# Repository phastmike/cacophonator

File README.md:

# Cacophonator

This repository contains the [KiCad](https://www.kicad.org/) project of a try at recreating an instance of
**[the cacophonator](https://www.theremin.us/Circuit_Library/cacophonator.html)**
by Arthur Harrison. 

### Build iteration

#### V1 THT

- Using THT (Through-hole) components
- Designed for [JSL 166x116x70mm Box](https://www.leroymerlin.pt/produtos/caixa-estanque-10-boquilhas-153x102x67mm-ip66-cinzento-jsl-15918315.html)

## Modifications to the original
 
- Added a potentiometer to control the output amplitude (volume)
   - Should be a **logaritmic (log) potentiometer**
- Added DC Input jack with diodes for multiple, concurrent, power sources
   - Battery (9V)
   - DC IN (9 or 12V))

## Notes

Designed with KiCad 9.0 

Top cover layout tryout

Box (166x116x70mm)

### BOM - Bill of Materials

[BOM](icad/outputs/v1/cacophonator-bom.ods)

### Links

- https://www.theremin.us/Circuit_Library/cacophonator.html
- https://syntherjack.net/catophonator/
- https://vitrolxul.mitiendanube.com/productos/cacophonator/
- http://analogmodularsystem.blogspot.com/2014/01/cacophonator-i.html
- https://milwaukeemakerspace.org/2011/09/cacophonator/
- https://beavisaudio.com/projects/cmossynthesizers/
- https://blacblob.qsdf.org/2018/10/03/cacophonator/
- https://static.flickr.com/100/312128991_4e7175fa40.jpg?v=0
- https://www.ti.com/lit/an/slyt336/slyt336.pdf?ts=1739280684395
- https://www.flickr.com/photos/53178019@N00/page2
- https://electro-music.com/forum/post-328159.html
- https://dimsos.dk/cacophonator/cacophonator-take-2-v8/
- https://www.matrixsynth.com/search/label/Cacophonator
- http://www.subtlenoisemaker.com/cacophonator_noir.html

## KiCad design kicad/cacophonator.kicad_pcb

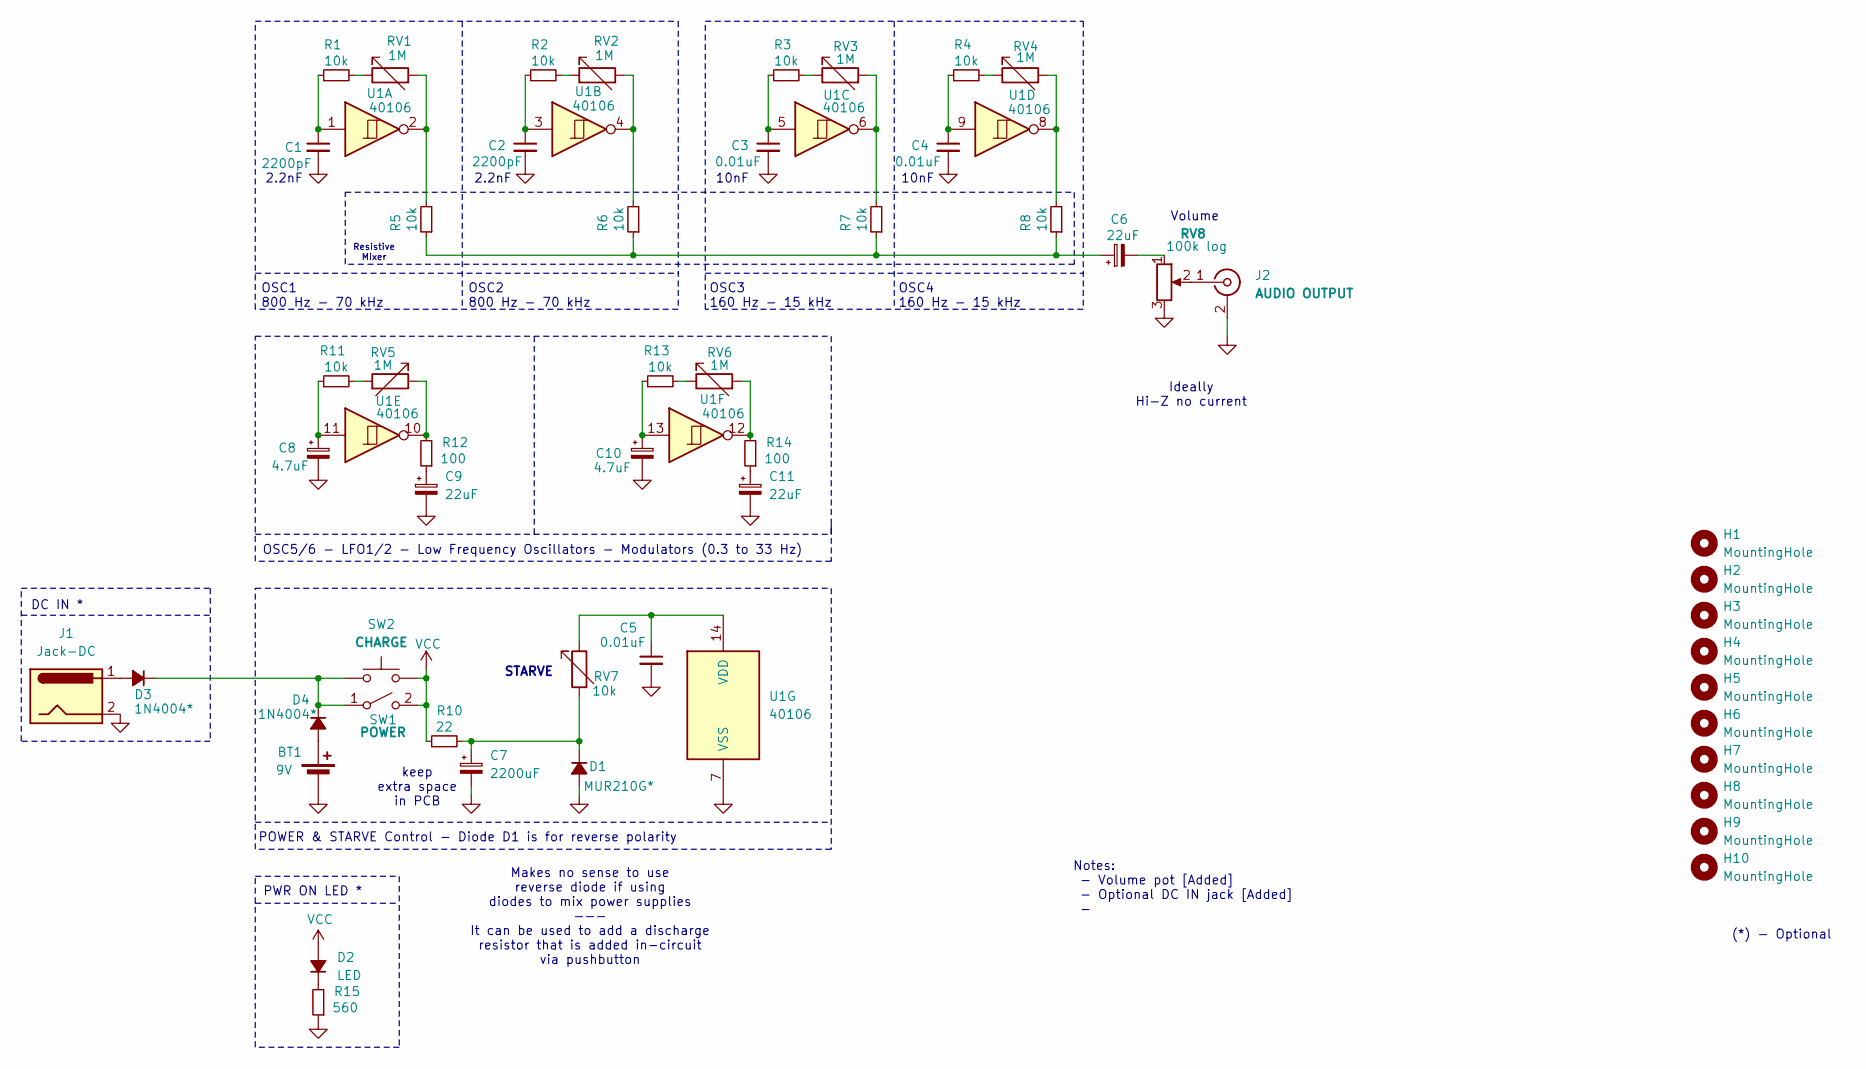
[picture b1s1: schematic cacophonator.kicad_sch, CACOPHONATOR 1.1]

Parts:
BT1: 9V; JST_PH_B2B-PH-K_1x02_P2.00mm_Vertical
C1, C2: 2200pF; C_Disc_D7.0mm_W2.5mm_P5.00mm
C3, C4, C5: 0.01uF; C_Disc_D7.0mm_W2.5mm_P5.00mm
C6: 22uF; CP_Radial_D4.0mm_P2.00mm
C7: 2200uF; CP_Radial_D10.0mm_P5.00mm
C8, C10: 4.7uF; CP_Radial_D4.0mm_P2.00mm
C9, C11: 22uF; CP_Radial_D7.5mm_P2.50mm
D1: MUR210G*; D_DO-35_SOD27_P7.62mm_Horizontal
D2: LED; JST_PH_B2B-PH-K_1x02_P2.00mm_Vertical
D3, D4: 1N4004*; D_DO-35_SOD27_P7.62mm_Horizontal
H1, H2, H3, H4, H5, H6, H7, H8, H9, H10: MountingHole; MountingHole_3.2mm_M3_ISO7380_Pad
J1: Jack-DC; JST_PH_B2B-PH-K_1x02_P2.00mm_Vertical
J2: AUDIO OUTPUT; JST_PH_B2B-PH-K_1x02_P2.00mm_Vertical
R1, R2, R3, R4, R5, R6, R7, R8, R11, R13: 10k; R_Axial_DIN0204_L3.6mm_D1.6mm_P5.08mm_Horizontal
R10: 22; R_Axial_DIN0204_L3.6mm_D1.6mm_P5.08mm_Horizontal
R12, R14: 100; R_Axial_DIN0204_L3.6mm_D1.6mm_P5.08mm_Horizontal
R15: 560; R_Axial_DIN0204_L3.6mm_D1.6mm_P5.08mm_Horizontal
RV1, RV2, RV3, RV4, RV5, RV6: 1M; JST_PH_B2B-PH-K_1x02_P2.00mm_Vertical
RV7: 10k; JST_PH_B2B-PH-K_1x02_P2.00mm_Vertical
RV8: 100k log; JST_PH_B3B-PH-K_1x03_P2.00mm_Vertical
SW1: POWER; JST_PH_B2B-PH-K_1x02_P2.00mm_Vertical
SW2: CHARGE; JST_PH_B2B-PH-K_1x02_P2.00mm_Vertical
U1: 40106; DIP-14_W7.62mm

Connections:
GND: BT1.2 (-), C1.2, C2.2, C3.2, C4.2, C5.2, C7.2, C8.2, C9.2, C10.2, C11.2, D1.2 (A), J1.2, J2.2 (Ext), R15.1, RV8.3, U1.7 (VSS)
unnamed: BT1.1 (+), D4.2 (A)
unnamed: C1.1, R1.1, U1.1
unnamed: C2.1, R2.1, U1.3
unnamed: C3.1, R3.1, U1.5
unnamed: C4.1, R4.1, U1.9
unnamed: C6.1, R5.1, R6.1, R7.1, R8.1
unnamed: C6.2, RV8.1
unnamed: C8.1, R11.1, U1.11
unnamed: C9.1, R12.1
unnamed: C10.1, R13.1, U1.13
unnamed: C11.1, R14.1
unnamed: C7.1, D1.1 (K), R10.2, RV7.2
unnamed: D2.1 (K), R15.2
unnamed: D3.2 (A), J1.1
unnamed: D3.1 (K), D4.1 (K), SW1.1 (A), SW2.1
unnamed: J2.1 (In), RV8.2
unnamed: R1.2, RV1.1
unnamed: R2.2, RV2.1
unnamed: R3.2, RV3.1
unnamed: R4.2, RV4.1
unnamed: R5.2, RV1.2, U1.2
unnamed: R6.2, RV2.2, U1.4
unnamed: R7.2, RV3.2, U1.6
unnamed: R8.2, RV4.2, U1.8
unnamed: R11.2, RV5.2
unnamed: R12.2, RV5.1, U1.10
unnamed: R13.2, RV6.1
unnamed: R14.2, RV6.2, U1.12
unnamed: C5.1, RV7.1, U1.14 (VDD)
VCC: D2.2 (A), R10.1, SW1.2 (B), SW2.2

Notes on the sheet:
OSC4 160 Hz - 15 kHz
Volume
10nF
Ideally Hi-Z no current
POWER & STARVE Control - Diode D1 is for reverse polarity
2.2nF
(*) - Optional
Resistive Mixer
DC IN *
STARVE
keep extra space in PCB
Makes no sense to use reverse diode if using diodes to mix power supplies --- It can be used to add a discharge resistor that is added in-circuit via pushbutton
PWR ON LED *
OSC1 800 Hz - 70 kHz
Notes: - Volume pot [Added] - Optional DC IN jack [Added] -
OSC3 160 Hz - 15 kHz
OSC2 800 Hz - 70 kHz
OSC5/6 - LFO1/2 - Low Frequency Oscillators - Modulators (0.3 to 33 Hz)

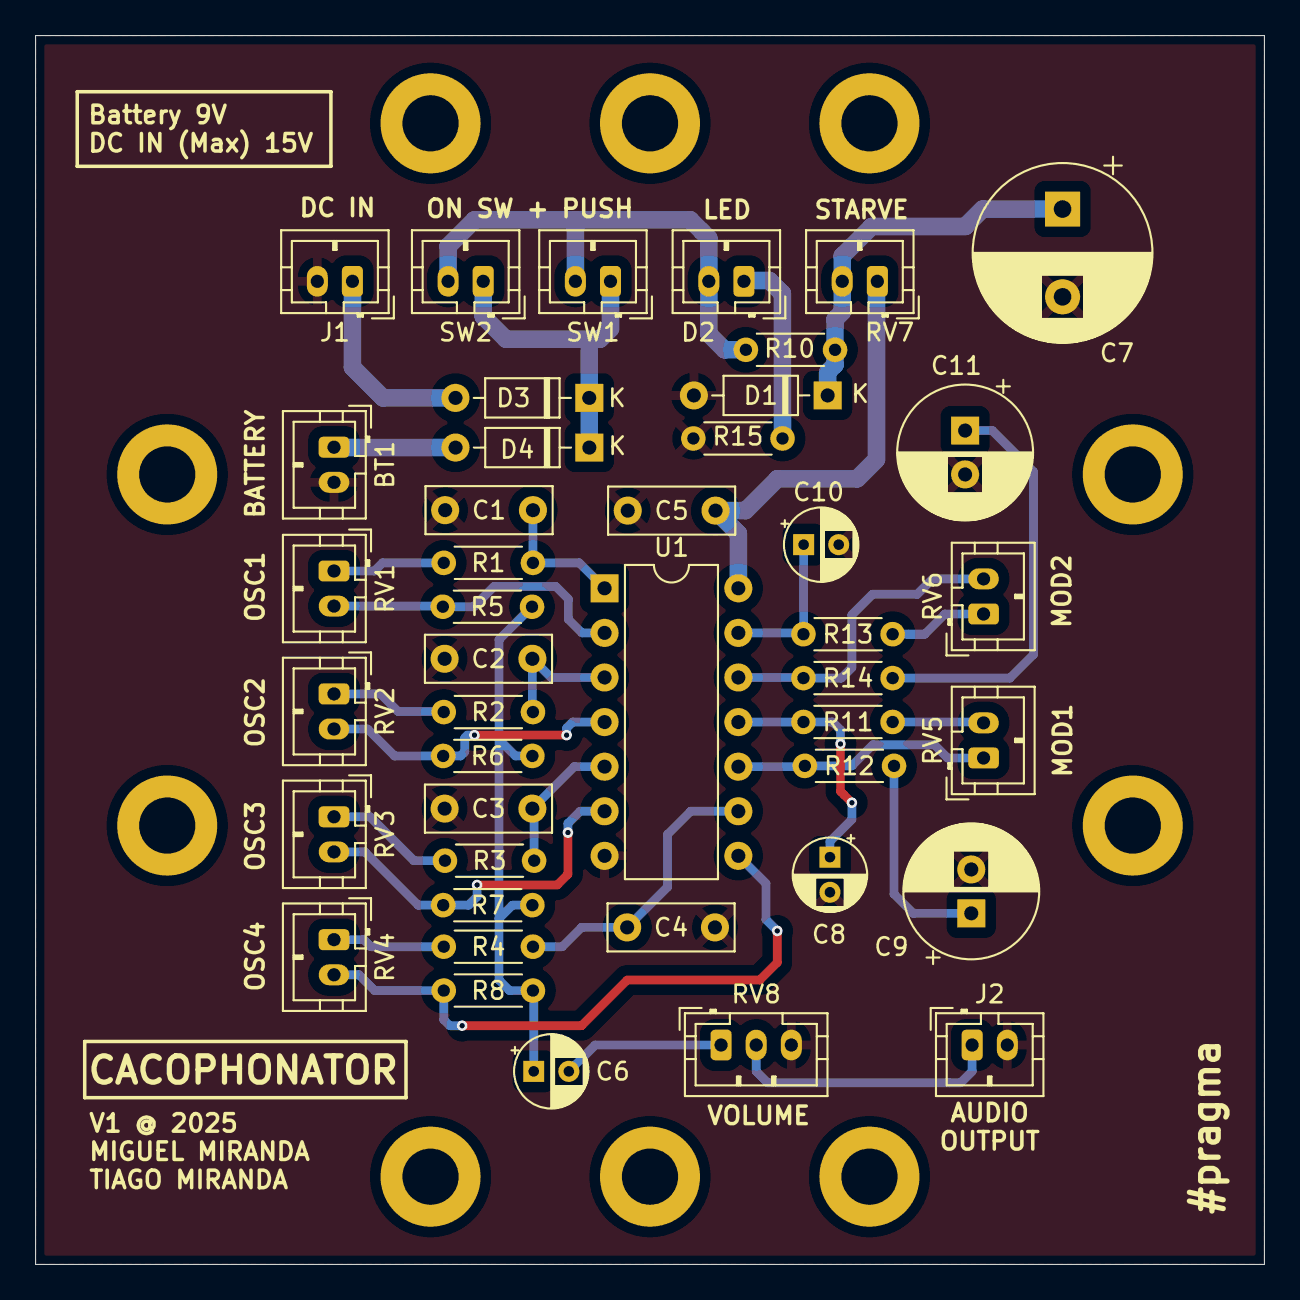
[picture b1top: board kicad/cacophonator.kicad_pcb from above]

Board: 2 copper layers, 70.0 x 70.0 mm, 53 parts (0 on the bottom side), 31 nets.

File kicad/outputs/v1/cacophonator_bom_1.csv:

"Reference";"Value";"Qty"
"BT1";"9V";"1"
"C1,C2";"2200pF";"2"
"C3,C4,C5";"0.01uF";"3"
"C6,C9,C11";"22uF";"3"
"C7";"2200uF";"1"
"C8,C10";"4.7uF";"2"
"D1";"MUR210G*";"1"
"D2";"LED";"1"
"D3,D4";"1N4004*";"2"
"J1";"Jack-DC";"1"
"J2";"AUDIO OUTPUT";"1"
"R1,R2,R3,R4,R5,R6,R7,R8,R11,R13,RV7";"10k";"11"
"R10";"22";"1"
"R12,R14";"100";"2"
"R15";"560";"1"
"RV1,RV2,RV3,RV4,RV5,RV6";"1M";"6"
"RV8";"100k log";"1"
"SW1";"POWER";"1"
"SW2";"CHARGE";"1"
"U1";"40106";"1"

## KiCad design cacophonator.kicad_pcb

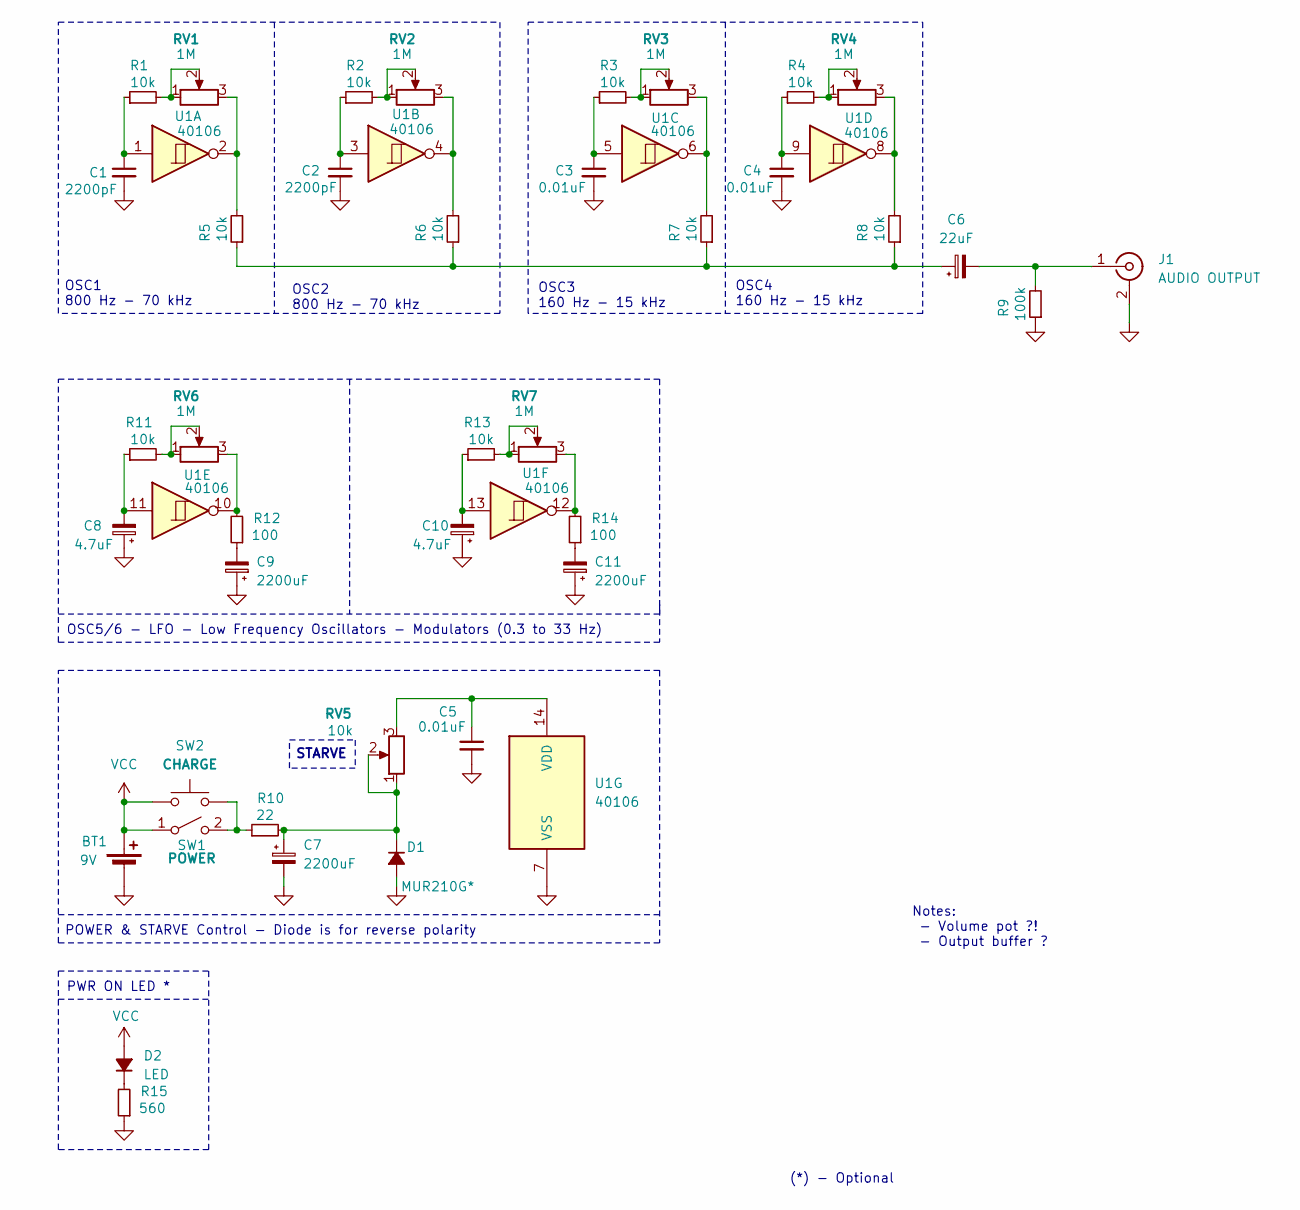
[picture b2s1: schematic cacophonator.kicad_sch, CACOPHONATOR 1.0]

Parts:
BT1: 9V; Molex_KK-254_AE-6410-02A_1x02_P2.54mm_Vertical
C1, C2: 2200pF; C_Disc_D7.0mm_W2.5mm_P5.00mm
C3, C4, C5: 0.01uF; C_Disc_D7.0mm_W2.5mm_P5.00mm
C6: 22uF; CP_Radial_D4.0mm_P2.00mm
C7, C9, C11: 2200uF; CP_Radial_D7.5mm_P2.50mm
C8, C10: 4.7uF; CP_Radial_D4.0mm_P2.00mm
D1: MUR210G*; D_DO-35_SOD27_P7.62mm_Horizontal
D2: LED; LED_D5.0mm
J1: AUDIO OUTPUT; Molex_KK-254_AE-6410-02A_1x02_P2.54mm_Vertical
R1, R2, R3, R4, R5, R6, R7, R8, R11, R13: 10k; R_Axial_DIN0204_L3.6mm_D1.6mm_P5.08mm_Horizontal
R9: 100k; R_Axial_DIN0204_L3.6mm_D1.6mm_P5.08mm_Horizontal
R10: 22; R_Axial_DIN0204_L3.6mm_D1.6mm_P5.08mm_Horizontal
R12, R14: 100; R_Axial_DIN0204_L3.6mm_D1.6mm_P5.08mm_Horizontal
R15: 560; R_Axial_DIN0204_L3.6mm_D1.6mm_P5.08mm_Horizontal
RV1, RV2, RV3, RV4, RV6, RV7: 1M; Molex_KK-254_AE-6410-03A_1x03_P2.54mm_Vertical
RV5: 10k; Molex_KK-254_AE-6410-03A_1x03_P2.54mm_Vertical
SW1: POWER; Molex_KK-254_AE-6410-02A_1x02_P2.54mm_Vertical
SW2: CHARGE; Molex_KK-254_AE-6410-02A_1x02_P2.54mm_Vertical
U1: 40106; DIP-14_W7.62mm

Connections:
GND: BT1.2 (-), C1.2, C2.2, C3.2, C4.2, C5.2, C7.2, C8.1, C9.1, C10.1, C11.1, D1.2 (A), J1.2 (Ext), R9.1, R15.1, U1.7 (VSS)
unnamed: C1.1, R1.1, U1.1
unnamed: C2.1, R2.1, U1.3
unnamed: C3.1, R3.1, U1.5
unnamed: C4.1, R4.1, U1.9
unnamed: C6.1, R5.1, R6.1, R7.1, R8.1
unnamed: C8.2, R11.1, U1.11
unnamed: C9.2, R12.1
unnamed: C10.2, R13.1, U1.13
unnamed: C11.2, R14.1
unnamed: C7.1, D1.1 (K), R10.2, RV5.1, RV5.2
unnamed: D2.1 (K), R15.2
unnamed: C6.2, J1.1 (In), R9.2
unnamed: R1.2, RV1.1, RV1.2
unnamed: R2.2, RV2.1, RV2.2
unnamed: R3.2, RV3.1, RV3.2
unnamed: R4.2, RV4.1, RV4.2
unnamed: R5.2, RV1.3, U1.2
unnamed: R6.2, RV2.3, U1.4
unnamed: R7.2, RV3.3, U1.6
unnamed: R8.2, RV4.3, U1.8
unnamed: R11.2, RV6.1, RV6.2
unnamed: R12.2, RV6.3, U1.10
unnamed: R13.2, RV7.1, RV7.2
unnamed: R14.2, RV7.3, U1.12
unnamed: R10.1, SW1.2 (B), SW2.2
unnamed: C5.1, RV5.3, U1.14 (VDD)
VCC: BT1.1 (+), D2.2 (A), SW1.1 (A), SW2.1

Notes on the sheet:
OSC5/6 - LFO - Low Frequency Oscillators - Modulators (0.3 to 33 Hz)
OSC4 160 Hz - 15 kHz
POWER & STARVE Control - Diode is for reverse polarity
(*) - Optional
STARVE
PWR ON LED *
OSC1 800 Hz - 70 kHz
Notes: - Volume pot ?! - Output buffer ?
OSC3 160 Hz - 15 kHz
OSC2 800 Hz - 70 kHz

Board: 2 copper layers, 40 parts (0 on the bottom side), 28 nets, no tracks yet.

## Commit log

2025-03-08 Added pdf folder with schematic and pcb layout
2025-03-08 updated schematic
2025-03-08 Minor changes
2025-03-08 Minor tweaks
2025-03-08 BOM added to README
2025-03-09 BOM Changes + minor tweaks
2025-03-09 Changed switch/push position on the layout
2025-03-09 Added box image
2025-03-09 More tweaks
2025-03-14 Minor updates
2025-03-19 Added info to schematic
2025-03-25 Minor tweak for local private data
